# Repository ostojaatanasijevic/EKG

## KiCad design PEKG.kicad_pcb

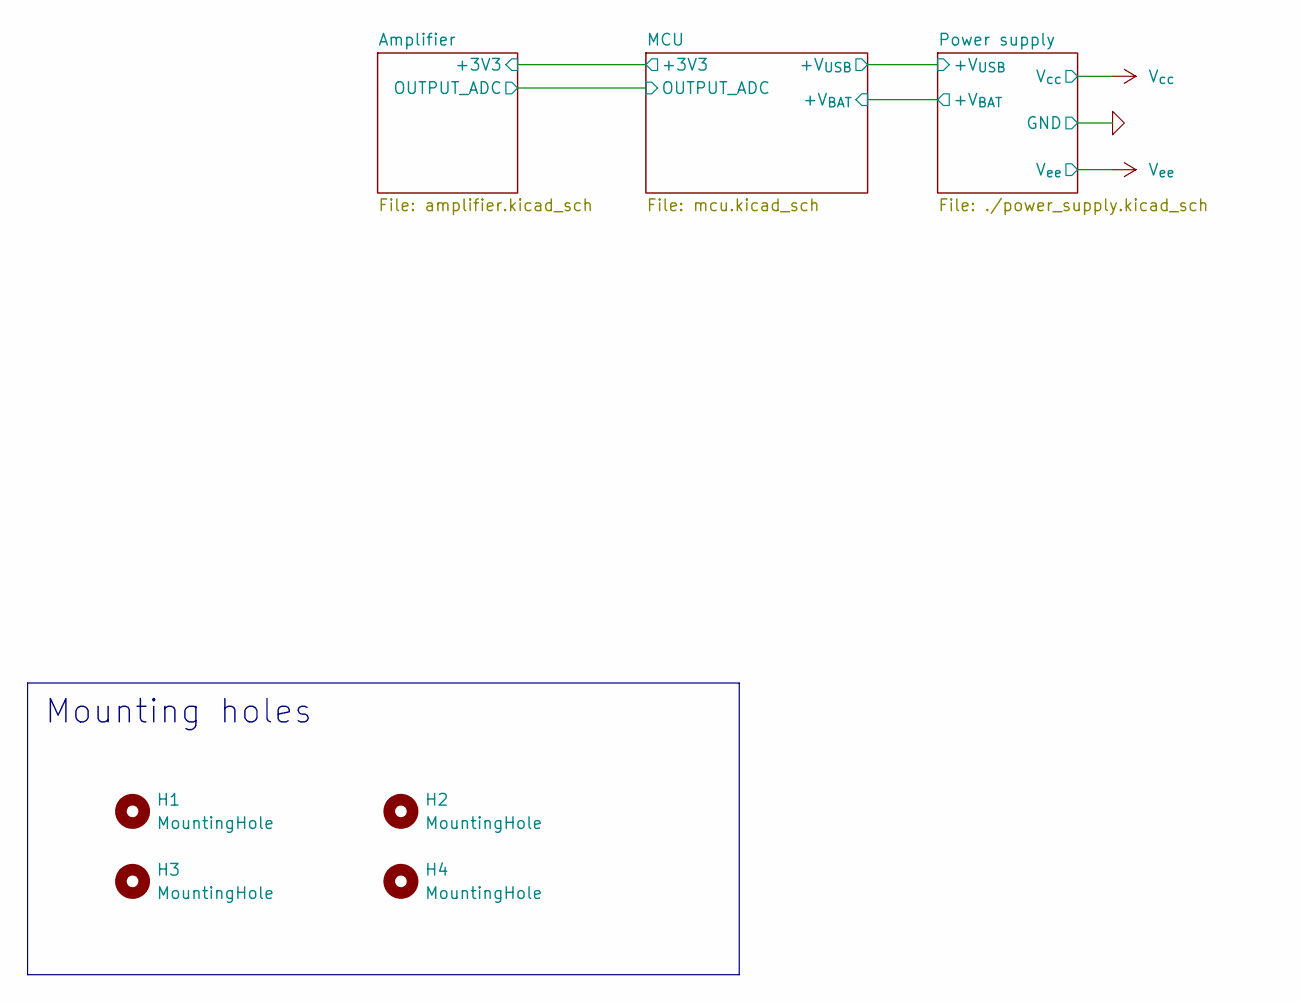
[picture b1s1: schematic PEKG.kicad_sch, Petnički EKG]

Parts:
H1, H2, H3, H4: MountingHole; MountingHole_3.2mm_M3_ISO14580_Pad_TopBottom

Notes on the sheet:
Mounting holes

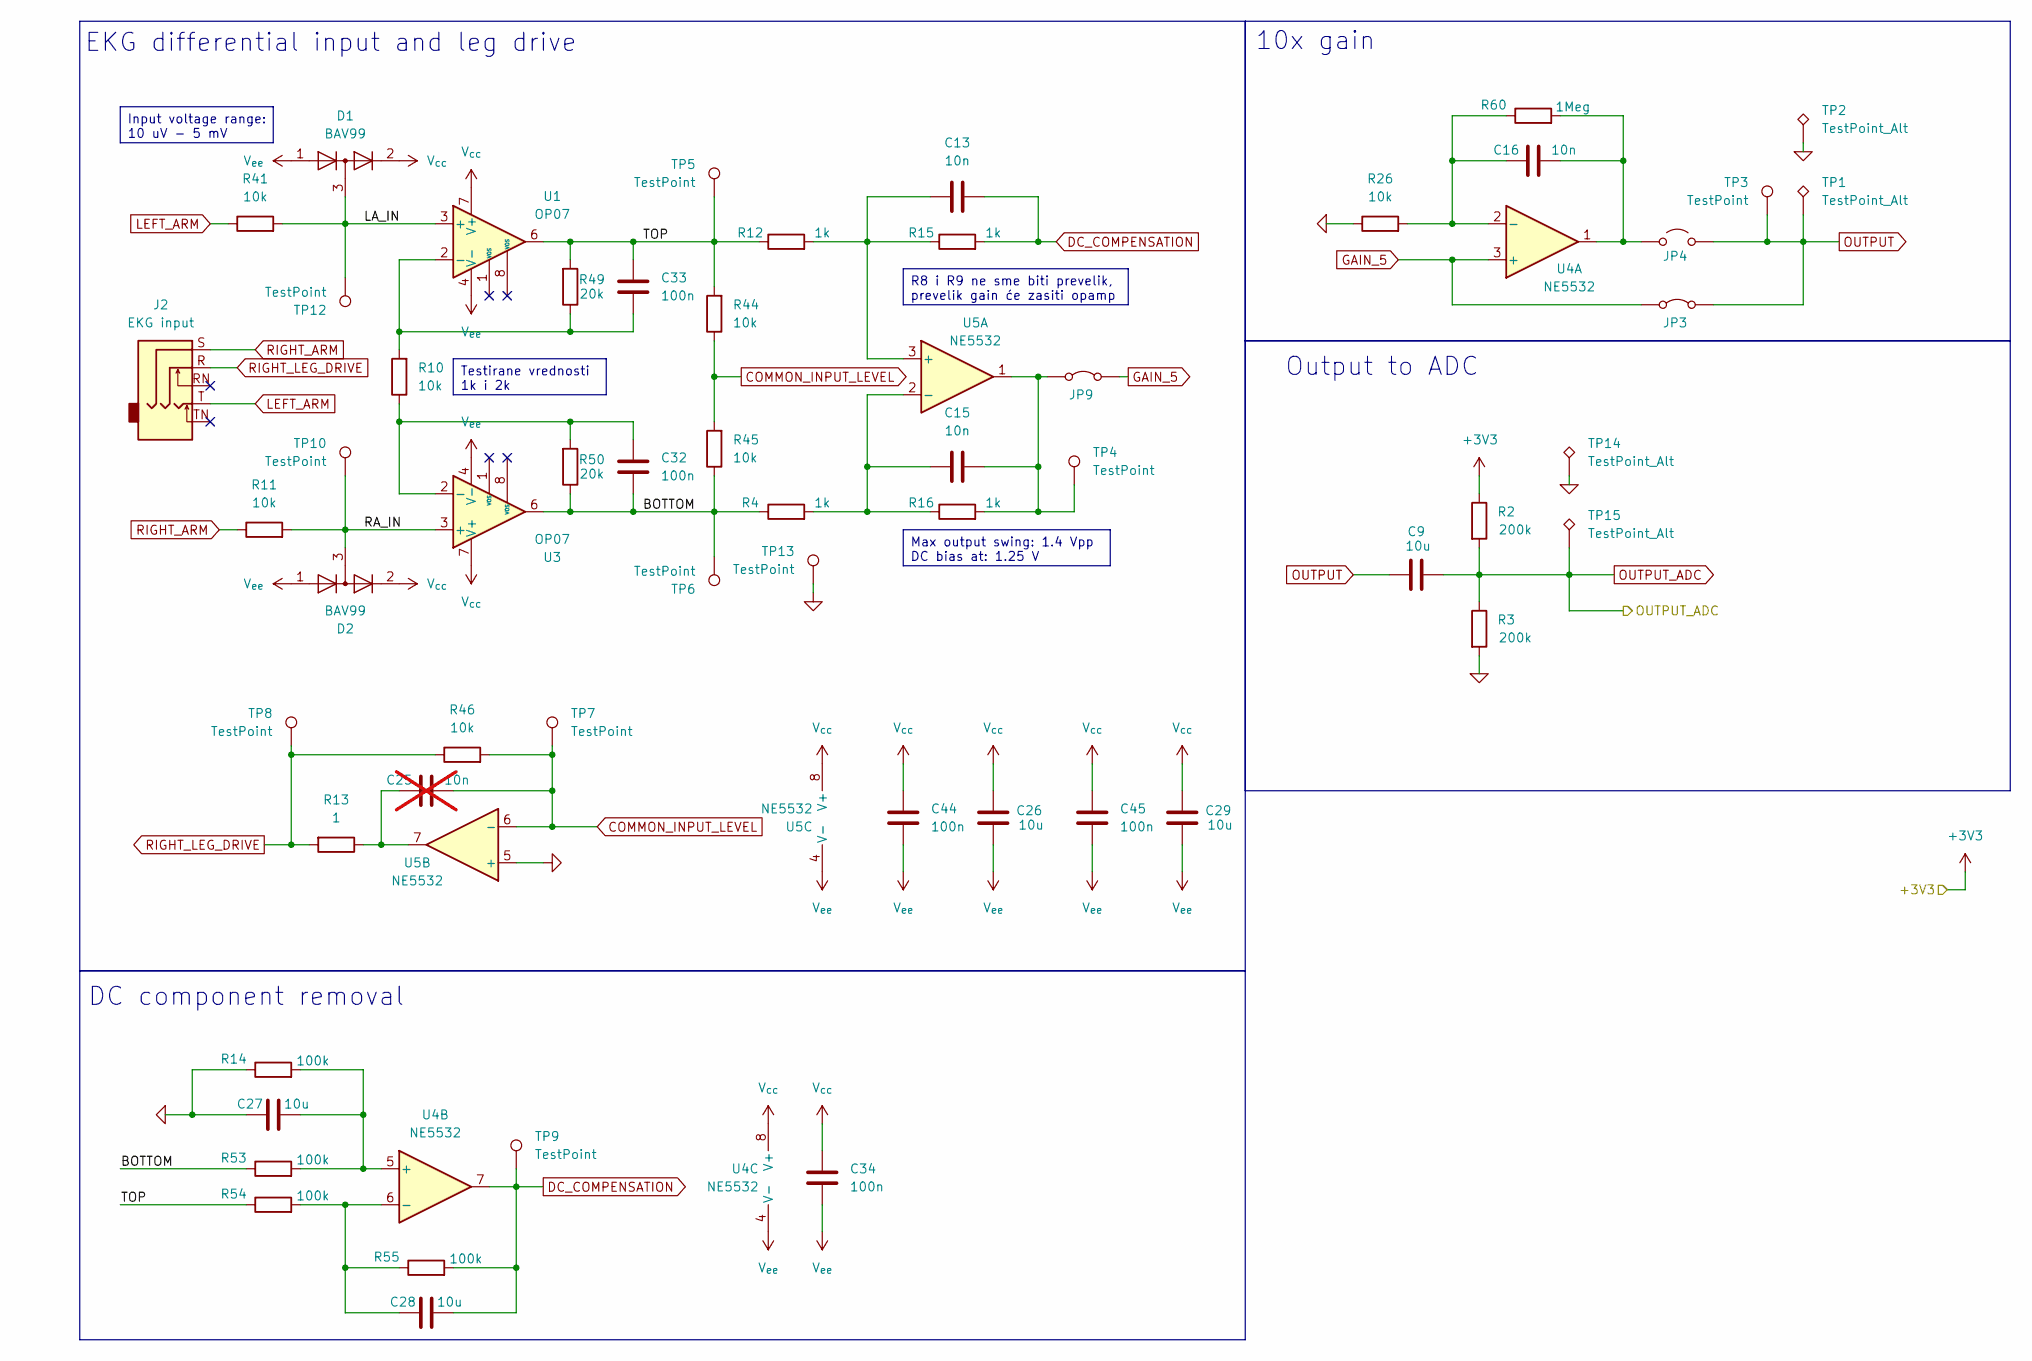
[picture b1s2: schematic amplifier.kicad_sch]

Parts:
C9, C26, C27, C28, C29: 10u; C_0603_1608Metric_Pad1.08x0.95mm_HandSolder; LCSC C96446
C13, C15, C16: 10n; C_0603_1608Metric_Pad1.08x0.95mm_HandSolder; LCSC C57112
C25: 10n; C_0603_1608Metric_Pad1.08x0.95mm_HandSolder; LCSC C57112; not fitted
C32, C33, C34, C44, C45: 100n; C_0603_1608Metric_Pad1.08x0.95mm_HandSolder; LCSC C14663
D1, D2: BAV99; SOT-23; LCSC C2500
J2: EKG input; Jack_3.5mm_CUI_SJ1-3525N_Horizontal
JP3, JP9: Jumper_2_Bridged; SolderJumper-2_P1.3mm_Bridged_RoundedPad1.0x1.5mm
JP4: Jumper_2_Open; SolderJumper-2_P1.3mm_Open_RoundedPad1.0x1.5mm
R2, R3: 200k; R_0603_1608Metric_Pad0.98x0.95mm_HandSolder; LCSC C25811
R4, R12, R15, R16: 1k; R_0603_1608Metric_Pad0.98x0.95mm_HandSolder; LCSC C21190
R10, R11, R26, R41, R44, R45, R46: 10k; R_0603_1608Metric_Pad0.98x0.95mm_HandSolder; LCSC C25804
R13: 1; R_0603_1608Metric_Pad0.98x0.95mm_HandSolder; LCSC C22936
R14, R53, R54, R55: 100k; R_0603_1608Metric_Pad0.98x0.95mm_HandSolder; LCSC C25803
R49, R50: 20k; R_0603_1608Metric_Pad0.98x0.95mm_HandSolder; LCSC C4184
R60: 1Meg; R_0603_1608Metric_Pad0.98x0.95mm_HandSolder; LCSC C22935
TP1, TP2, TP14, TP15: TestPoint_Alt; PinHeader_1x01_P2.54mm_Vertical
TP3, TP4, TP5, TP6, TP7, TP8, TP9, TP10, TP12, TP13: TestPoint; TestPoint_Pad_D3.0mm
U1, U3: OP07; SOIC-8_3.9x4.9mm_P1.27mm
U4, U5: NE5532; SOIC-8_3.9x4.9mm_P1.27mm

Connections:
0: C27.1, R3.2, R14.1, R26.1, TP2.1 (1_1), TP13.1 (1_1), TP14.1 (1_1), U5.5 (+); also elsewhere on the board
+3V3: R2.1; also elsewhere on the board
/Amplifier/BOTTOM: C32.1, R4.1, R45.1, R50.1, R53.1, TP6.1 (1_1), U3.6
/Amplifier/LA_IN: D1.3 (K), R41.2, TP12.1 (1_1), U1.3 (+)
/Amplifier/RA_IN: D2.3 (K), R11.2, TP10.1 (1_1), U3.3 (+)
/Amplifier/TOP: C33.2, R12.1, R44.2, R49.2, R54.1, TP5.1 (1_1), U1.6
COMMON_INPUT_LEVEL: C25.1, R44.1, R45.2, R46.2, TP7.1 (1_1), U5.6 (-)
DC_COMPENSATION: C13.1, C28.2, R15.2, R55.2, TP9.1 (1_1), U4.7
GAIN_5: JP3.1 (A), JP9.2 (B), U4.3 (+)
LEFT_ARM: J2.T, R41.1
unnamed: C25.2, R13.1, U5.7
unnamed: C16.1, JP4.1 (A), R60.2, U4.1
unnamed: C15.1, JP9.1 (A), R16.2, TP4.1 (1_1), U5.1
unnamed: C33.1, R10.2, R49.1, U1.2 (-)
unnamed: C32.2, R10.1, R50.2, U3.2 (-)
unnamed: C16.2, R26.2, R60.1, U4.2 (-)
unnamed: C27.2, R14.2, R53.2, U4.5 (+)
unnamed: C28.1, R54.2, R55.1, U4.6 (-)
unnamed: C13.2, R12.2, R15.1, U5.3 (+)
unnamed: C15.2, R4.2, R16.1, U5.2 (-)
OUTPUT: C9.1, JP3.2 (B), JP4.2 (B), TP1.1 (1_1), TP3.1 (1_1)
OUTPUT_ADC: C9.2, R2.2, R3.1, TP15.1 (1_1); also elsewhere on the board
RIGHT_ARM: J2.S, R11.1
RIGHT_LEG_DRIVE: J2.R, R13.2, R46.1, TP8.1 (1_1)
V_{cc}: C26.1, C29.1, C34.2, C44.2, C45.2, D1.2 (A), D2.2 (A), U1.7 (V+), U3.7 (V+), U4.8 (V+), U5.8 (V+); also elsewhere on the board
V_{ee}: C26.2, C29.2, C34.1, C44.1, C45.1, D1.1 (K), D2.1 (K), U1.4 (V-), U3.4 (V-), U4.4 (V-), U5.4 (V-); also elsewhere on the board

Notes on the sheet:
EKG differential input and leg drive
Output to ADC
10x gain
DC component removal
Input voltage range: 10 uV - 5 mV
Testirane vrednosti 1k i 2k
R8 i R9 ne sme biti prevelik, prevelik gain će zasiti opamp
Max output swing: 1.4 Vpp DC bias at: 1.25 V

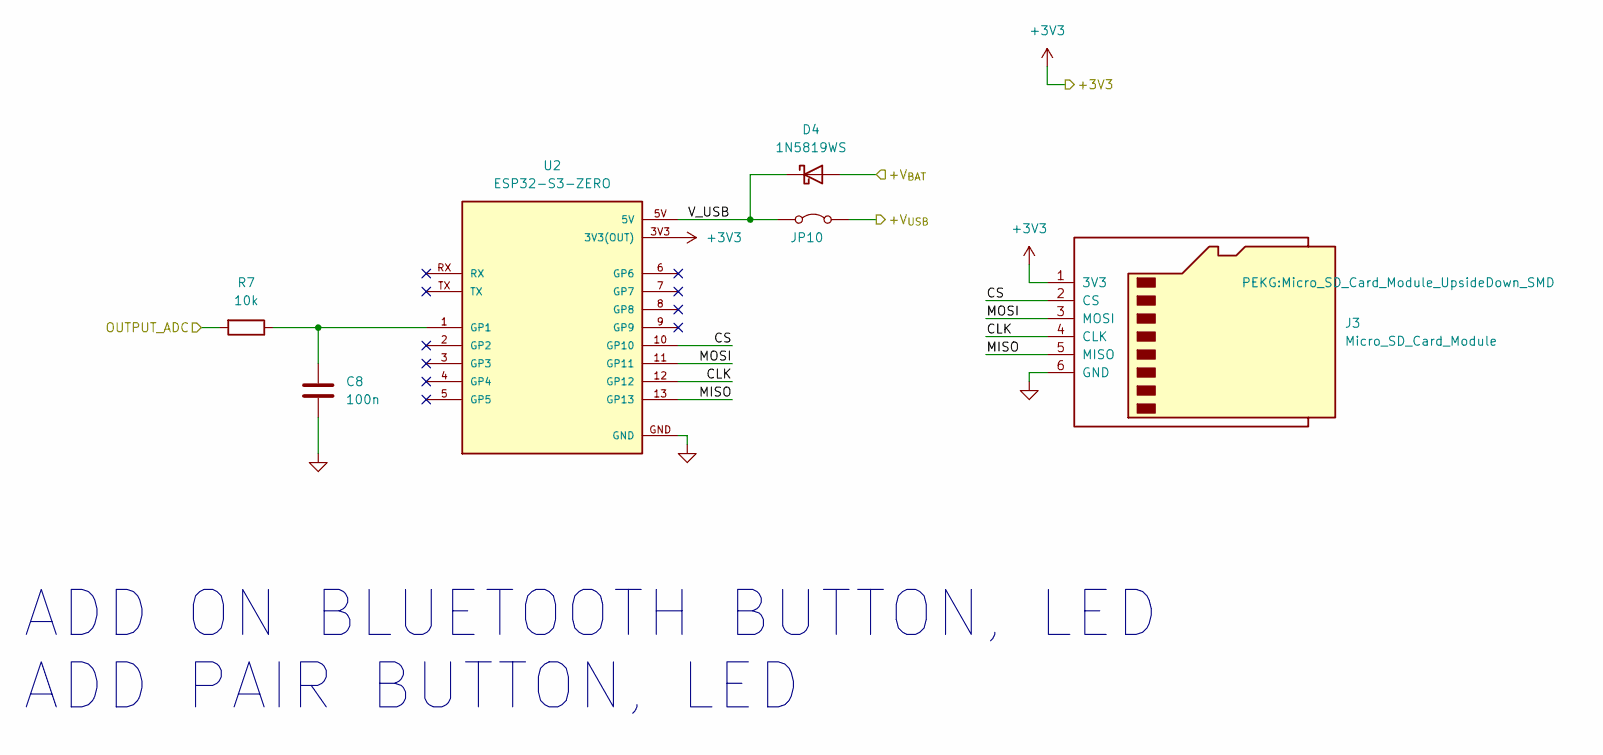
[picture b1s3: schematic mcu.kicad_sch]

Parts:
C8: 100n; C_0603_1608Metric_Pad1.08x0.95mm_HandSolder; LCSC C14663
D4: 1N5819WS; D_SOD-323; LCSC C191023
J3: Micro_SD_Card_Module; Micro_SD_Card_Module_UpsideDown_SMD
JP10: Jumper_2_Bridged; SolderJumper-2_P1.3mm_Bridged_RoundedPad1.0x1.5mm
R7: 10k; R_0603_1608Metric_Pad0.98x0.95mm_HandSolder; LCSC C25804
U2: ESP32-S3-ZERO; MODULE_ESP32-S3-ZERO_SMD; PARTREV NA

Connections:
0: C8.1, J3.6 (GND), U2.GND; also elsewhere on the board
+3V3: J3.1 (3V3), U2.3V3 (3V3(OUT)); also elsewhere on the board
+V_{BAT}: D4.2 (A); also elsewhere on the board
+V_{USB}: JP10.2 (B); also elsewhere on the board
/MCU/CLK: J3.4 (CLK), U2.12 (GP12)
/MCU/CS: J3.2 (CS), U2.10 (GP10)
/MCU/MISO: J3.5 (MISO), U2.13 (GP13)
/MCU/MOSI: J3.3 (MOSI), U2.11 (GP11)
/MCU/V_USB: D4.1 (K), JP10.1 (A), U2.5V
unnamed: C8.2, R7.1, U2.1 (GP1)
OUTPUT_ADC: R7.2; also elsewhere on the board

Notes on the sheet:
ADD ON BLUETOOTH BUTTON, LED ADD PAIR BUTTON, LED

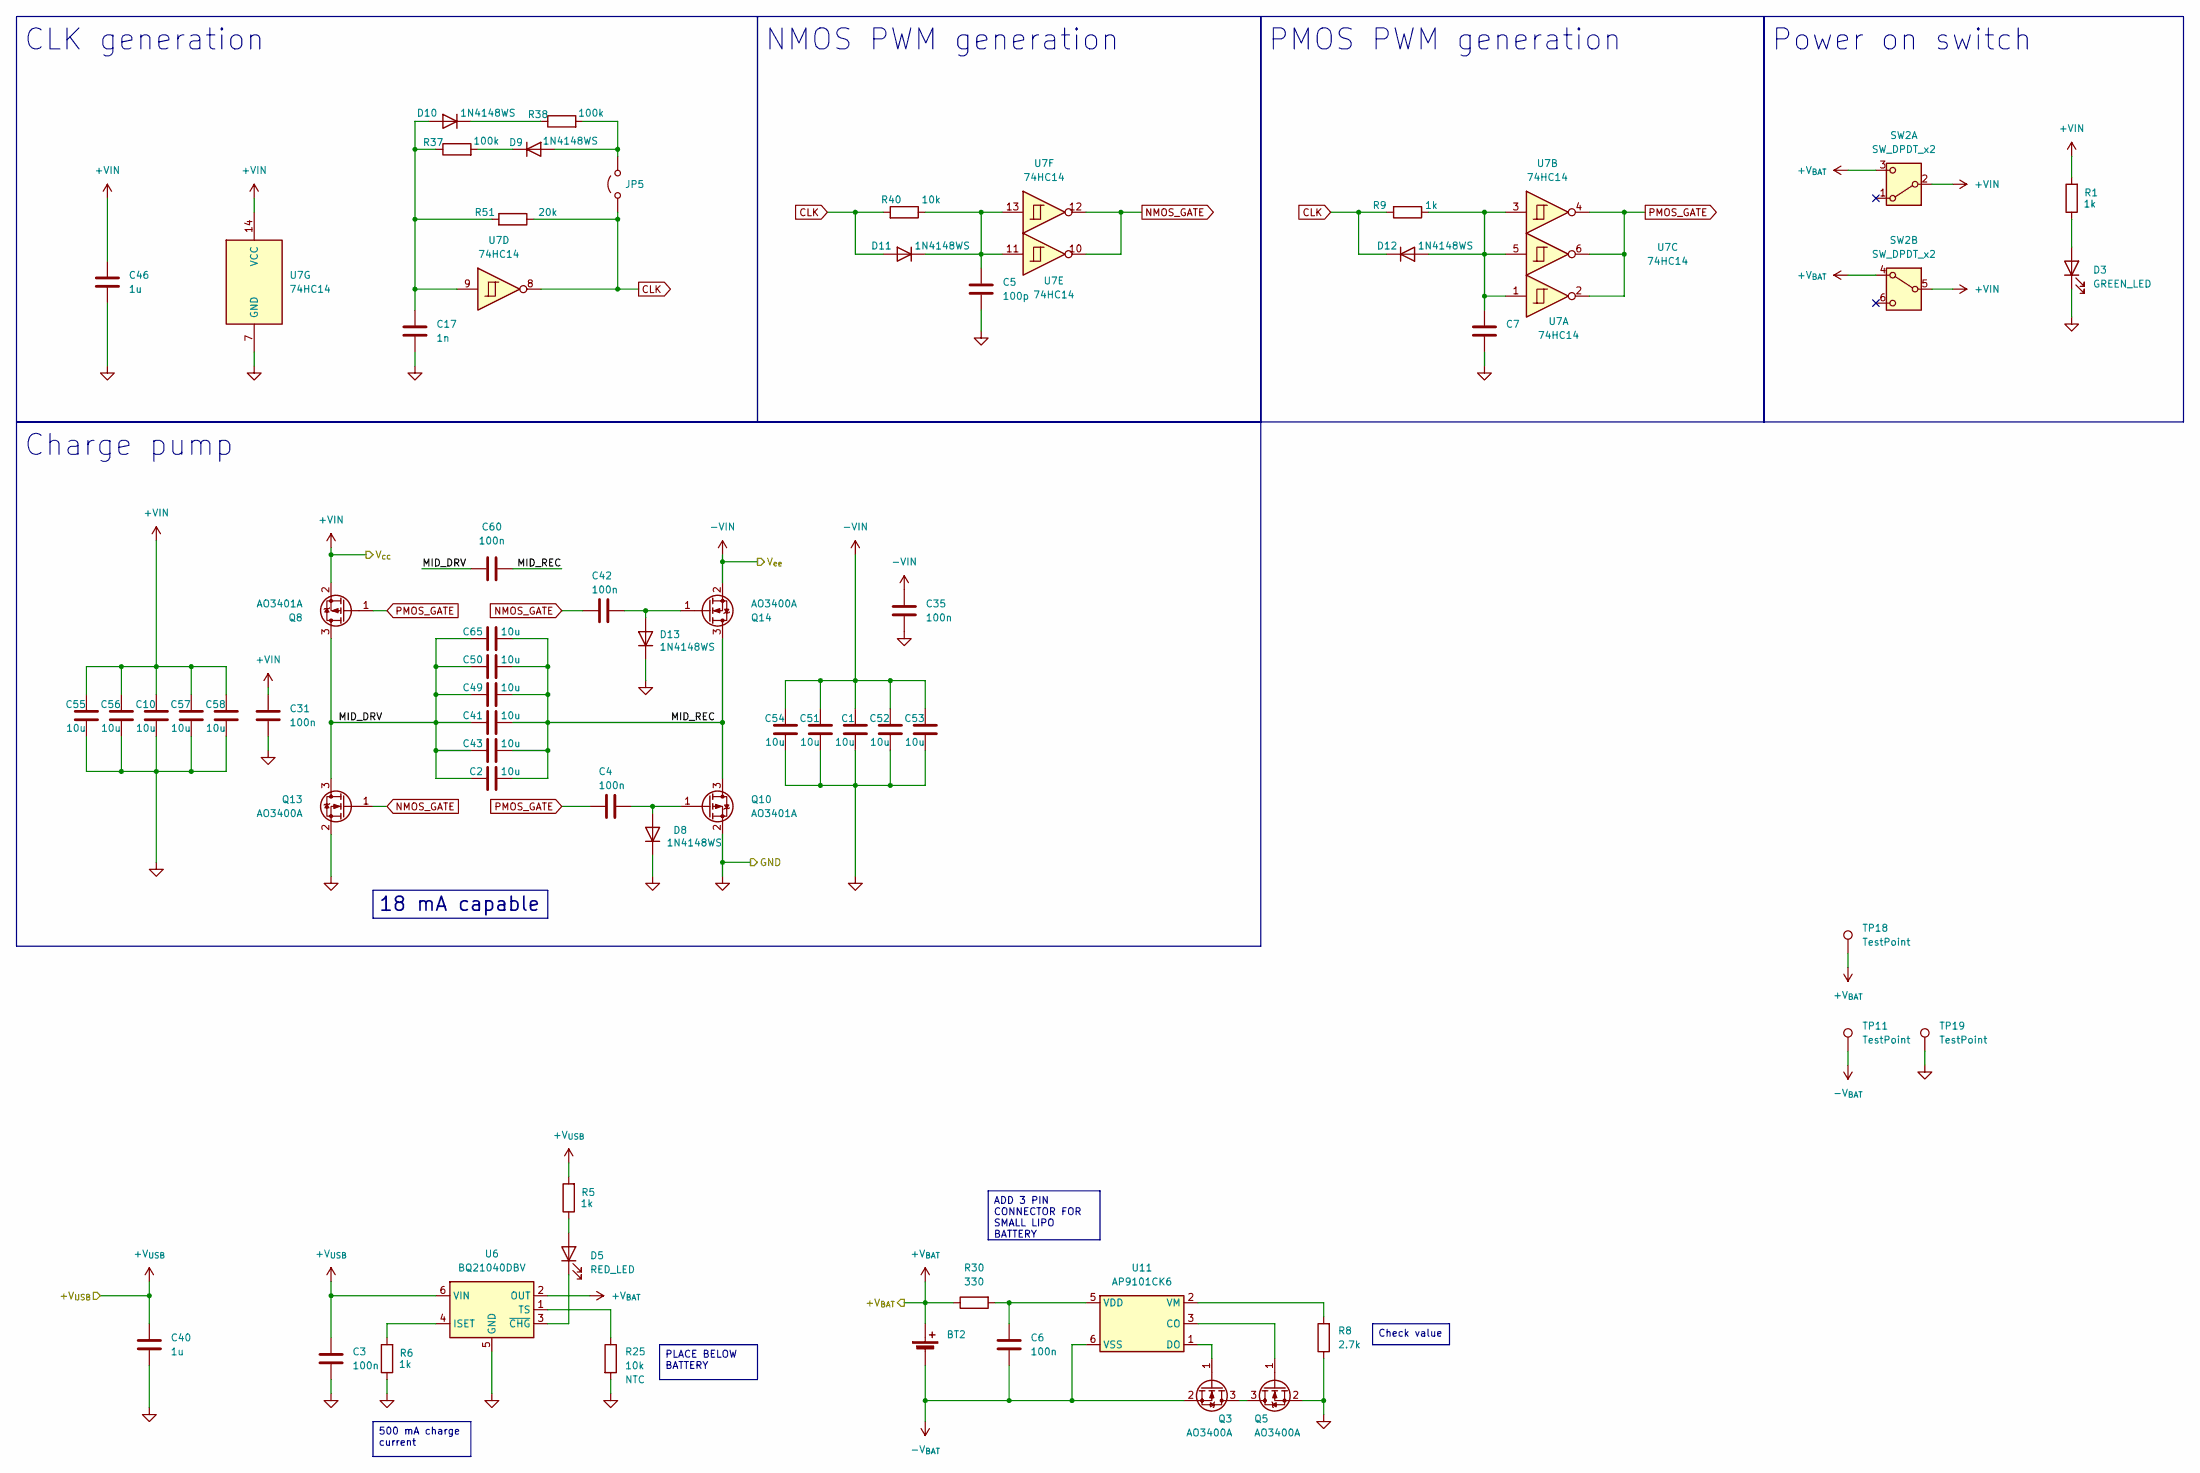
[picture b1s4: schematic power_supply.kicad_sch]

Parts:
BT2: Battery_Cell; battery_holder
C1, C2, C10, C41, C43, C49, C50, C51, C52, C53, C54, C55, C56, C57, C58, C65: 10u; R_0805_2012Metric_Pad1.20x1.40mm_HandSolder; Voltage 25V; LCSC C15850
C3, C4, C6, C31, C35, C42, C60: 100n; C_0603_1608Metric_Pad1.08x0.95mm_HandSolder; LCSC C14663
C5, C7: 100p; C_0603_1608Metric_Pad1.08x0.95mm_HandSolder; LCSC C14858
C17: 1n; C_0603_1608Metric_Pad1.08x0.95mm_HandSolder; LCSC C1588
C40, C46: 1u; C_0603_1608Metric_Pad1.08x0.95mm_HandSolder; LCSC C15849
D3: GREEN_LED; LED_0805_2012Metric_Pad1.15x1.40mm_HandSolder; LCSC C2297
D5: RED_LED; LED_0805_2012Metric_Pad1.15x1.40mm_HandSolder; LCSC C84256
D8, D9, D10, D11, D12, D13: 1N4148WS; D_SOD-323; LCSC C2128
JP5: Jumper_2_Open; SolderJumper-2_P1.3mm_Open_RoundedPad1.0x1.5mm
Q3, Q5, Q13, Q14: AO3400A; SOT-23; LCSC C20917
Q8, Q10: AO3401A; SOT-23; LCSC C15127
R1, R5, R6, R9: 1k; R_0603_1608Metric_Pad0.98x0.95mm_HandSolder; LCSC C21190
R8: 2.7k; R_0603_1608Metric_Pad0.98x0.95mm_HandSolder; LCSC C13167
R25, R40: 10k; R_0603_1608Metric_Pad0.98x0.95mm_HandSolder; LCSC C25804
R30: 330; R_0603_1608Metric_Pad0.98x0.95mm_HandSolder; LCSC C23138
R37, R38: 100k; R_0603_1608Metric_Pad0.98x0.95mm_HandSolder; LCSC C25803
R51: 20k; R_0603_1608Metric_Pad0.98x0.95mm_HandSolder; LCSC C4184
SW2: SW_DPDT_x2; SW_EG1271
TP11, TP18, TP19: TestPoint; TestPoint_Pad_D3.0mm
U6: BQ21040DBV; SOT-23-6
U7: 74HC14; SOIC-14_3.9x8.7mm_P1.27mm
U11: AP9101CK6; SOT-23-6_Handsoldering

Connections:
0: C1.1, C3.1, C5.1, C7.1, C10.1, C17.1, C31.1, C35.1, C40.1, C46.1, C51.1, C52.1, C53.1, C54.1, C55.1, C56.1, C57.1, C58.1, D3.1 (K), D8.1 (K), D13.1 (K), Q5.2 (S), Q10.2 (S), Q13.2 (S), R6.1, R8.1, R25.2, TP19.1 (1_1), U6.5 (GND), U7.7 (GND); also elsewhere on the board
+V_{BAT}: BT2.1 (+), R30.1, SW2.3 (C), SW2.4 (A), SW2.6 (C), TP18.1 (1_1), U6.2 (OUT); also elsewhere on the board
+V_{USB}: C3.2, C40.2, R5.2, U6.6 (VIN); also elsewhere on the board
-V_{BAT}: BT2.2 (-), C6.1, Q3.2 (S), TP11.1 (1_1), U11.6 (VSS)
/Power supply/MID_DRV: C2.1, C41.1, C43.1, C49.1, C50.1, C60.2, C65.1, Q8.3 (D), Q13.3 (D)
/Power supply/MID_REC: C2.2, C41.2, C43.2, C49.2, C50.2, C60.1, C65.2, Q10.3 (D), Q14.3 (D)
CLK: D11.2 (A), D12.1 (K), JP5.1 (A), R9.2, R40.2, R51.1, U7.8
NMOS_GATE: C42.1, Q13.1 (G), U7.10, U7.12
unnamed: D3.2 (A), R1.1
unnamed: D5.2 (A), R5.1
unnamed: D5.1 (K), U6.3 (~CHG)
unnamed: C4.2, D8.2 (A), Q10.1 (G)
unnamed: D9.2 (A), JP5.2 (B), R38.2
unnamed: D9.1 (K), R37.2
unnamed: C17.2, D10.2 (A), R37.1, R51.2, U7.9
unnamed: D10.1 (K), R38.1
unnamed: C5.2, D11.1 (K), R40.1, U7.11, U7.13
unnamed: C7.2, D12.2 (A), R9.1, U7.1, U7.3, U7.5
unnamed: C42.2, D13.2 (A), Q14.1 (G)
unnamed: Q3.3 (D), Q5.3 (D)
unnamed: Q3.1 (G), U11.1 (DO)
unnamed: Q5.1 (G), U11.3 (CO)
unnamed: R6.2, U6.4 (ISET)
unnamed: R25.1, U6.1 (TS)
unnamed: C6.2, R30.2, U11.5 (VDD)
unnamed: R8.2, U11.2 (VM)
PMOS_GATE: C4.1, Q8.1 (G), U7.2, U7.4, U7.6
V_{cc}: C10.2, C31.2, C46.2, C55.2, C56.2, C57.2, C58.2, Q8.2 (S), R1.2, SW2.2 (B), SW2.5 (B), U7.14 (VCC); also elsewhere on the board
V_{ee}: C1.2, C35.2, C51.2, C52.2, C53.2, C54.2, Q14.2 (S); also elsewhere on the board

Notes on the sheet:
Power on switch
Charge pump
CLK generation
NMOS PWM generation
PMOS PWM generation
Check value
ADD 3 PIN CONNECTOR FOR SMALL LIPO BATTERY
PLACE BELOW BATTERY
500 mA charge current
18 mA capable

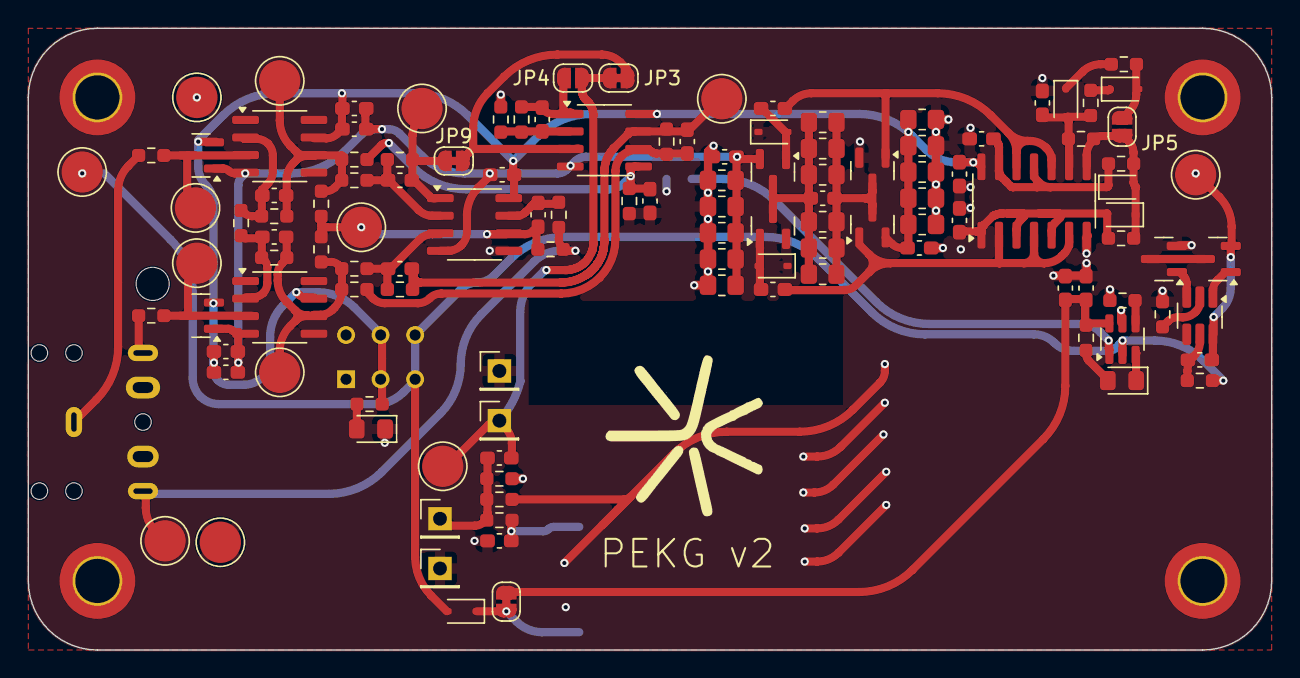
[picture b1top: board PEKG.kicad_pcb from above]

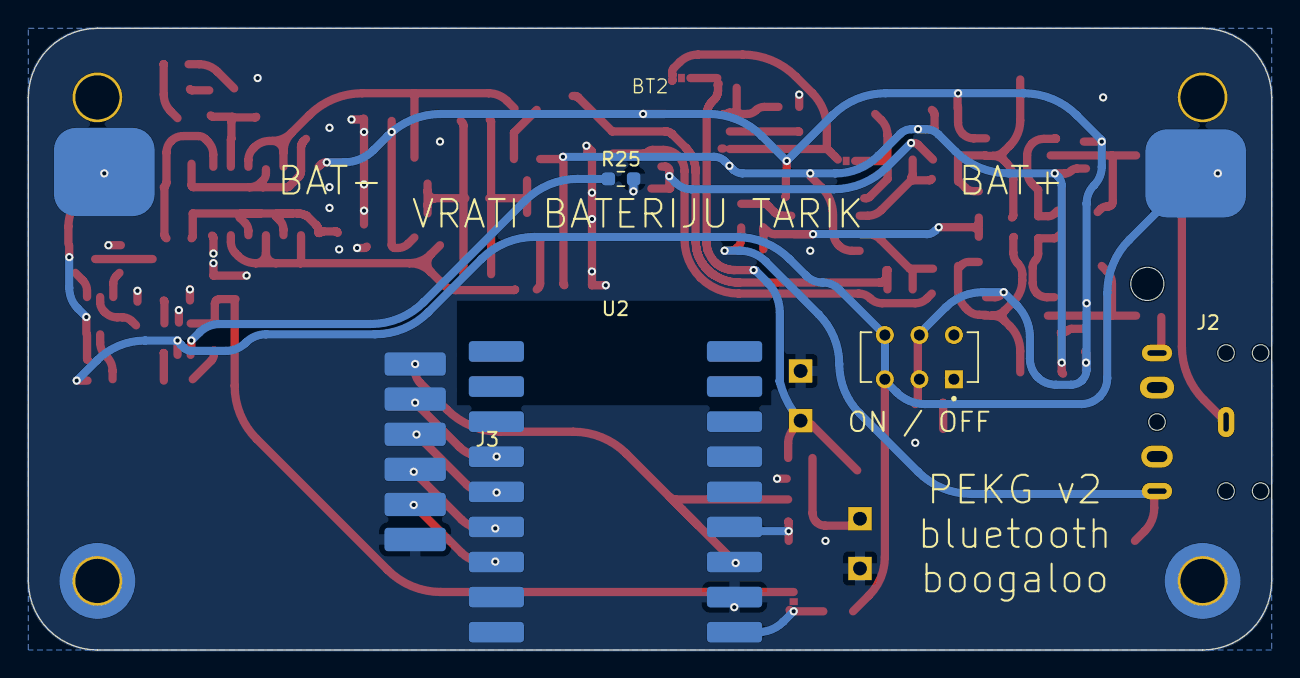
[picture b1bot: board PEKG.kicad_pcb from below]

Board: 2 copper layers, 90.0 x 45.0 mm, 131 parts (6 on the bottom side), 58 nets.

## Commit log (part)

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2025-03-27 Init.
2025-03-28 Fun with rounded traces.
2025-03-28 Changed input opamps to NCS.
2025-03-30 Added stages, todos.
2025-03-30 Added README.
2025-03-30 Minor update.
2025-03-31 Little PCB modifications.
2025-04-07 Tad saner schematic.
2025-04-07 Newwww
2025-04-07 Added sir.
2025-04-07 Removed some
2025-04-07 Rm clk
2025-04-07 Updated values added note.
2025-04-11 Updates schematic, tests.
    Fixed git issue
2025-04-11 Updated scripts, schematic
2025-04-12 ništa
2025-04-13 Notchfilter added.
2025-04-14 Most all commonents linked to LCSC.
2025-04-15 Ideje???
2025-05-24 Inst. amp. added, rough placement done.
2025-05-25 Fixed incorrect filter and gain amp circuits.
2025-05-25 Input detection checked in simulation.
2025-05-25 Added testpoints.
2025-05-26 Schematic done.
2025-05-26 Rutiranje gotovo.
2025-05-26 Rounded traces??? fixed silkscreen.
2025-05-26 Readme.
2025-06-08 Updated leg drive, output connector, boost converter.
2025-06-09 Updated input conn, updated battery holder.
2025-11-21 bandstop sim update.
2025-12-31 all hail JFET.
2026-04-06 Fixed inverted DC off, reduced gain from 500 to 5
2026-04-06 added sw
2026-04-07 opop
2026-05-18 added notes, changed opamps
2026-05-19 more readable schematic, bipolar supply
2026-05-21 Added ESP32-S3
2026-05-21 sd card
2026-05-21 connected SD and ESP
2026-05-22 updated form factor and placment
2026-05-23 ADC, levels
